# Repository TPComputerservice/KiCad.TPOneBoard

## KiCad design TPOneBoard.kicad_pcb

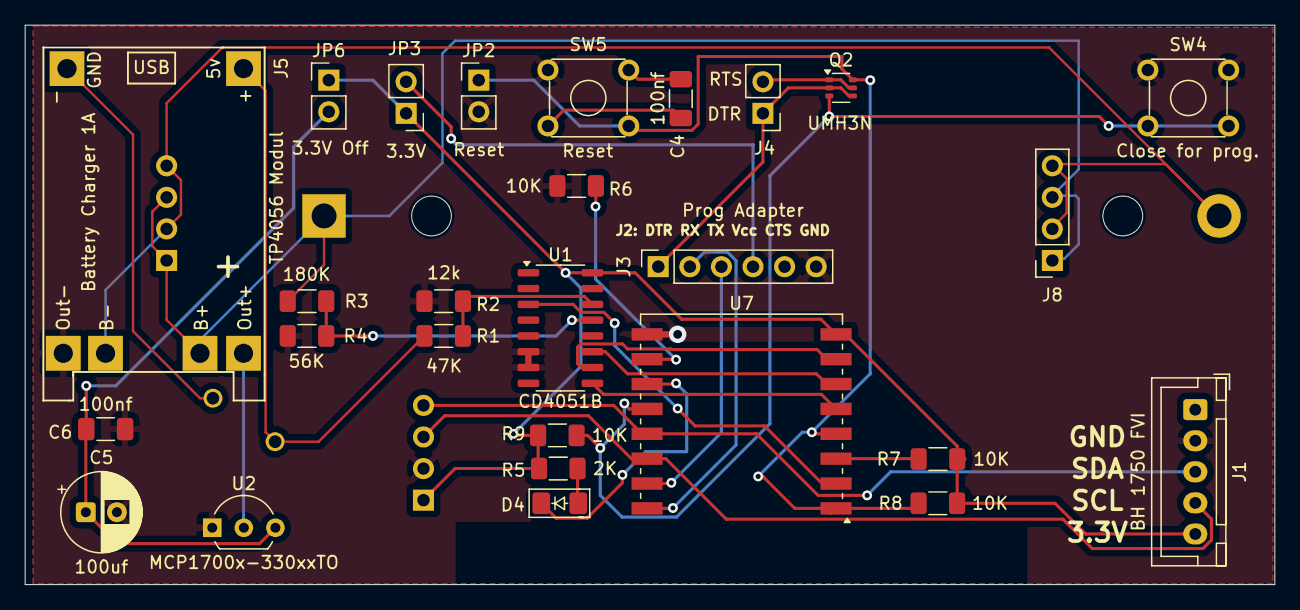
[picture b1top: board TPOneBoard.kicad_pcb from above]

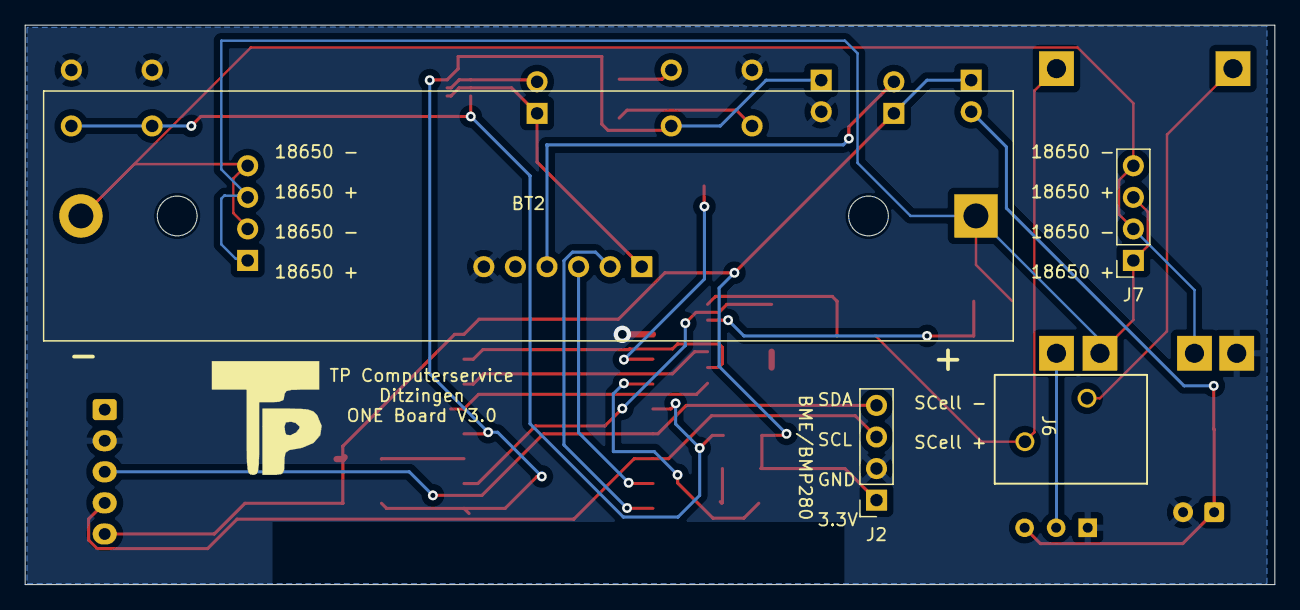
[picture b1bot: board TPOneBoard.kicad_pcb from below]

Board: 2 copper layers, 100.5 x 45.0 mm, 31 parts (4 on the bottom side), 29 nets.

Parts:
BT2: Battery_Cell; BatteryHolder_MPD_BH-18650-PC2
C4, C6: 100nf; C_1206_HandSolder
C5: 100uf; CP_Radial_D6.3mm_P2.50mm
D4: LED; LED_1206_3216_TPC_Metric_Pad1.42x1.75mm_HandSolder
J1: BH 1750 FVI; JST_XH_B5B-XH-A_1x05_P2.50mm_Vertical
J2: BME/BMP280; PinSocket_1x04_P2.54mm_Vertical
J3: Conn_01x06_Pin; PinSocket_1x06_P2.54mm_Vertical
J4: Conn_01x02_Pin; PinHeader_1x02_P2.54mm_Vertical
J5: TP4056 Modul; TP4056-18650
J6: Screw_Terminal_01x02; WAGO_250_202_1x2_TPC
J7, J8: Conn_01x04_Socket; PinSocket_1x04_P2.54mm_Vertical
JP2: Reset; PinHeader_1x02_P2.54mm_Vertical
JP3: 3.3V; PinHeader_1x02_P2.54mm_Vertical
JP6: 3.3V Off; PinHeader_1x02_P2.54mm_Vertical
Q2: UMH3N; SOT-363_SC-70-6
R1: 47K; R_1206_HandSolder
R2: 12k; R_1206_HandSolder
R3: 180K; R_1206_HandSolder
R4: 56K; R_1206_HandSolder
R5: 2K; R_1206_HandSolder
R6, R7, R8, R9: 10K; R_1206_HandSolder
SW4: Close for prog.; SW_TH_Tactile_Omron
SW5: Reset; SW_TH_Tactile_Omron
U1: CD4051B; SO-16_3.9x9.9mm_P1.27mm
U2: MCP1700x-330xxTO; TO-92L_Inline_Wide
U7: ESP-07S; ESP-07

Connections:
4056 Out+: J5.3, U2.2 (VI)
18650+: BT2.1 (+), J5.5, J7.1, J7.3, J8.1, J8.3, R3.1
18650-: BT2.2 (-), J5.6, J7.2, J7.4, J8.2, J8.4
+3.3V: J1.5, J2.1, JP3.1 (A), JP6.1 (A), R5.2, R7.2, R8.2, R9.2, U1.16 (VDD), U7.8 (VCC)
ADC: U1.3 (X), U7.2 (ADC)
Akku: R3.2, R4.1, U1.13 (X0)
DTR: J3.1, J4.1, Q2.2 (B1), Q2.4 (E2)
DeepS: JP2.1 (A), Q2.6 (C1), R8.1, SW5.4 (A), U7.1 (REST), U7.4 (GPIO16)
EN: R7.1, U7.3 (CH_PD)
GND: C5.2, C6.2, J1.2, J2.2, J3.6, J5.4, JP2.2 (B), R2.2, R4.2, R6.2, SW4.1, SW4.2, SW5.1, U1.6 (INH), U1.7 (VEE), U2.1 (GND), U7.9 (GND)
IO0: Q2.3 (C2), R9.1, SW4.3 (K), SW4.4 (A), U7.12 (GPIO0)
IO12: U1.11 (A), U7.6 (GPIO12)
IO13: U1.10 (B), U7.7 (GPIO13)
IO14: U1.9 (C), U7.5 (GPIO14)
LED_Buildin: D4.1 (K), U7.11 (GPIO2)
unnamed: C4.1, SW5.2
unnamed: D4.2 (A), R5.1
unnamed: J3.4, JP3.2 (B)
unnamed: C5.1, C6.1, JP6.2 (B), U2.3 (VO)
unnamed: C4.2, SW5.3 (K)
unnamed: R6.1, U7.10 (GPIO15)
RTS: J4.2, Q2.1 (E1), Q2.5 (B2)
RXD: J3.3, U7.15 (RXD)
SCL: J1.4, J2.3, U7.14 (GPIO5)
SCell+: J5.1, J6.1, R1.1
SCell-: J5.2, J6.2
SDA: J1.3, J2.4, U7.13 (GPIO4)
SolarPanel: R1.2, R2.1, U1.14 (X1)
TXD: J3.2, U7.16 (TXD)

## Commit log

2025-07-25 Initial commit von TPOneBoard
2025-07-26 1. Stufe
2025-07-30 Platine Bestellt am 30.07.2025 Signed-off-by: TPComputerservice <78719315+TPComputerservice@users.noreply.github.com>
2025-07-30 Zip Files für bestellte Platine vom 30.07.2025
